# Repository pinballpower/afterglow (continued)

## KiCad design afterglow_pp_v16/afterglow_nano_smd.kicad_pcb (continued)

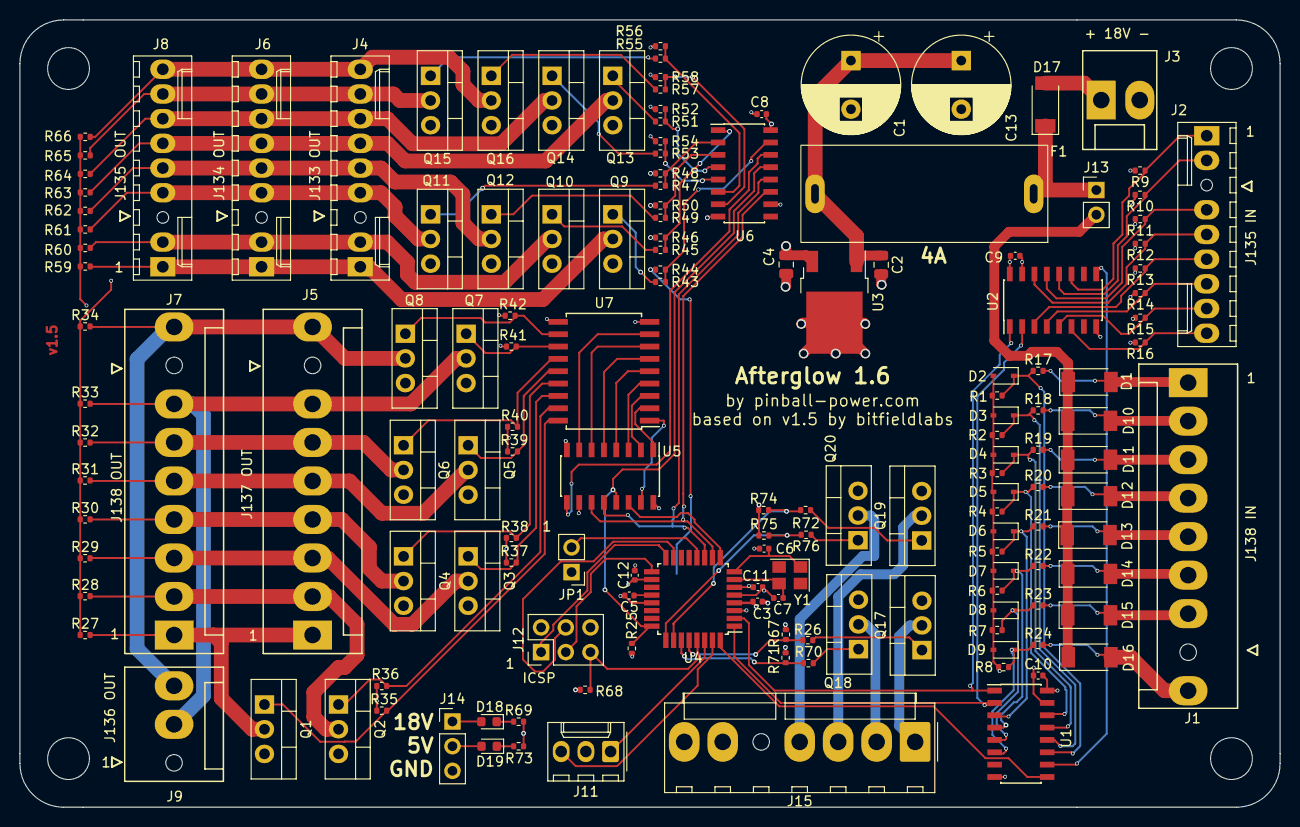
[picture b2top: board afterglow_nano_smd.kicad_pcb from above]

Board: 4 copper layers, 129.7 x 81.0 mm, 156 parts (0 on the bottom side), 111 nets.

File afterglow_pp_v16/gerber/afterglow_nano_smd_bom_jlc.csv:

"Comment","Designator","Footprint","LCSC Part #"
"1000uF","C1","CP_Radial_D16.0mm_P7.50mm","C10750"
"0.33","C2,C4","C_0805_HandSoldering","C1740"
"0.1","C3","C_0805_HandSoldering","C49678"
"RB080","D1,D10,D11,D12,D13,D14,D15,D16,D17","SOD-128","C50603"
"4.7V","D2,D3,D4,D5,D6,D7,D8,D9","D_SOD-323_HandSoldering","C124651"
"5A SB","F1","Fuseholder5x20_horiz_open_lateral_Type-II","C3130"
"J137_IN_C","J1","Molex_KK-41791-9_9x3.96mm_Straight","C239400"
"J133_IN_R","J2","Molex_KK-6410-09_09x2.54mm_Straight","C509152"
"Conn_Power","J3","Molex_KK-41791-02_02x3.96mm_Straight","C239393"
"J133_OUT_R","J4","Molex_KK-6410-09_09x2.54mm_Straight","C509152"
"J137_OUT_C","J5","Molex_KK-41791-9_9x3.96mm_Straight","C239400"
"J134_OUT_R","J6","Molex_KK-6410-09_09x2.54mm_Straight","C509152"
"J138_OUT_C","J7","Molex_KK-41791-9_9x3.96mm_Straight","C239400"
"J135_OUT_R","J8","Molex_KK-6410-09_09x2.54mm_Straight","C509152"
"136_OUT_C","J9","Molex_KK-41791-03_03x3.96mm_Straight","C10585"
"FQP11P06","Q1,Q2,Q3,Q4,Q5,Q6,Q7,Q8","TO-220_Vertical","C693361"
"FQP13N06L","Q9,Q10,Q11,Q12,Q13,Q14,Q15,Q16","TO-220_Vertical","C243082"
"1k","R1,R2,R3,R4,R5,R6,R7,R8,R9,R10,R11,R12,R13,R14,R15,R16,R17,R18,R19,R20,R21,R22,R23,R24","R_0805_HandSoldering","C17513"
"10k","R25,R27,R28,R29,R30,R31,R32,R33,R34,R44,R46,R48,R50,R52,R54,R56,R58,R59,R60,R61,R62,R63,R64,R65,R66","R_0805_HandSoldering","C17414"
"0.22","R26","R_2512_HandSoldering","C68608"
"2k","R35,R36,R37,R38,R39,R40,R41,R42","R_0805_HandSoldering","C17604"
"220","R43,R45,R47,R49,R51,R53,R55,R57","R_0805_HandSoldering","C17557"
"0","R67","R_Axial_DIN0207_L6.3mm_D2.5mm_P2.54mm_Vertical","C17477"
"CFG","SW1","SW_DIP_x4_W7.62mm_Slide","C559139"
"74LS165","U1,U2","SOIC-16_3.9x9.9mm_Pitch1.27mm","C5613"
"5V_Regulator","U3","TO-220_Vertical","C111887"
"74HC595","U5,U6","SOIC-16_3.9x9.9mm_Pitch1.27mm","C5947"
"ULN2803A","U7","SOIC-18W_7.5x11.6mm_Pitch1.27mm","C9683"

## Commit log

2023-01-06 Added new Pinball Power versions
2023-01-06 Finalized (?) v3
2023-01-07 Added new PP versions of Afterglow and Afterglow WS
2023-01-07 Update parts
2023-01-07 Afterglow 1.6
2023-01-07 Fix 3D settings
2023-01-07 Updated 3D settings
2023-01-07 Add mappings
2023-01-07 Passed DRC
